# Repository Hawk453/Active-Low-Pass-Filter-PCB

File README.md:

# Second-Order Active Low-Pass Filter (LM741)  

## Overview  

This project implements a **second-order active low-pass filter** using the **LM741 operational amplifier**. The filter is designed in **KiCad** and is suitable for basic signal conditioning and noise filtering applications.  

The filter attenuates frequencies above a specified **cutoff frequency (fc)** while allowing lower-frequency signals to pass with minimal attenuation.  

## Schematic  

## PCB Layout  

Here’s a preview of the designed PCB:  

The filter circuit is built using a **Sallen-Key topology** and includes:  

- **Op-Amp**: LM741 (U1)  
- **Resistors**: R1, R2, R3, R4  
- **Capacitors**: C1, C2  
- **Input/Output**: J1, J2 (Coaxial connectors), J3 (Pin connector)  
- **Power Supply**: ±10V  

*(Replace component values and results below with your actual design)*

| Component | Value       |
|-----------|-------------|
| R1        | 3.3 kΩ      |
| R2        | 3.3 kΩ      |
| R3, R4    | 10 kΩ       |
| C1        | 10 nF       |
| C2        | 10 nF       |
| Cutoff    | ~4.8 kHz    |  

## Files Included  

📁 **KiCad Project Files**  
- Schematic: `Second_Order_Low_Pass_Filter_Ac.kicad_sch`  
- PDF Schematic: `Second_Order_Low_Pass_Filter_Ac.pdf`  
- PCB Layout: `Second_Order_Low_Pass_Filter_Ac.kicad_pcb`  

📁 **Fabrication Files**  
- **Gerber Files**: Ready for PCB manufacturing.  
- Drill files and fabrication layers included.  

📁 **Bill of Materials (BOM)**  
- Can be generated from KiCad (`Tools` -> `Generate BOM`).  

## How to Use  

1. **View Schematic and PCB**  
   - Open `.kicad_sch` and `.kicad_pcb` files in **KiCad** (v9.0.2 or newer).  

2. **Simulate (Optional)**  
   - Export netlist and simulate in a tool like LTspice or use KiCad’s simulator for basic analysis.  

3. **Fabricate PCB**  
   - Use the included **Gerber files** to manufacture the PCB through a PCB fabrication service.  

4. **Assemble the Circuit**  
   - Solder components as per the schematic and BOM.  
   - Power the board using ±10V.  

5. **Test the Filter**  
   - Apply test signals and verify the cutoff frequency response using an oscilloscope or signal analyzer.  

## Notes  

- The **LM741** is a general-purpose op-amp with limited bandwidth. For high-frequency applications, consider alternatives like TL072 or LM358.  
- This filter is ideal for **audio applications** or low-frequency signal conditioning tasks.  

## License  

GPL 3.0

## Acknowledgments  

Special thanks to the **KiCad community** for making open-source hardware design accessible!

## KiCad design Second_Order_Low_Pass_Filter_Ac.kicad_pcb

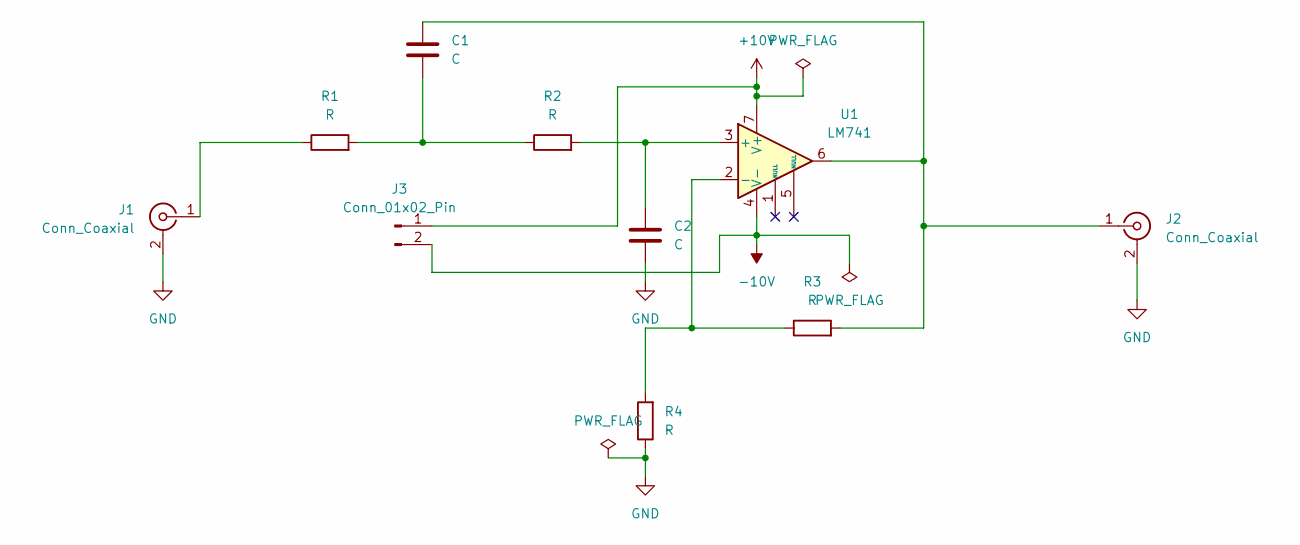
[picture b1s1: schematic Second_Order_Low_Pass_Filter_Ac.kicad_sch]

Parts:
C1, C2: C; C_Disc_D5.0mm_W2.5mm_P5.00mm
J1, J2: Conn_Coaxial; BNC_TEConnectivity_1478035_Horizontal
J3: Conn_01x02_Pin; Banana_Jack_2Pin
R1, R2, R3, R4: R; R_Axial_DIN0204_L3.6mm_D1.6mm_P7.62mm_Horizontal
U1: LM741; DIP-8_W7.62mm_LongPads

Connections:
+10V: J3.1, U1.7 (V+)
-10V: J3.2, U1.4 (V-)
GND: C2.2, J1.2 (Ext), J2.2 (Ext), R4.1
unnamed: C1.2, R1.2, R2.1
unnamed: J1.1 (In), R1.1
unnamed: C1.1, J2.1 (In), R3.2, U1.6
unnamed: C2.1, R2.2, U1.3 (+)
unnamed: R3.1, R4.2, U1.2 (-)

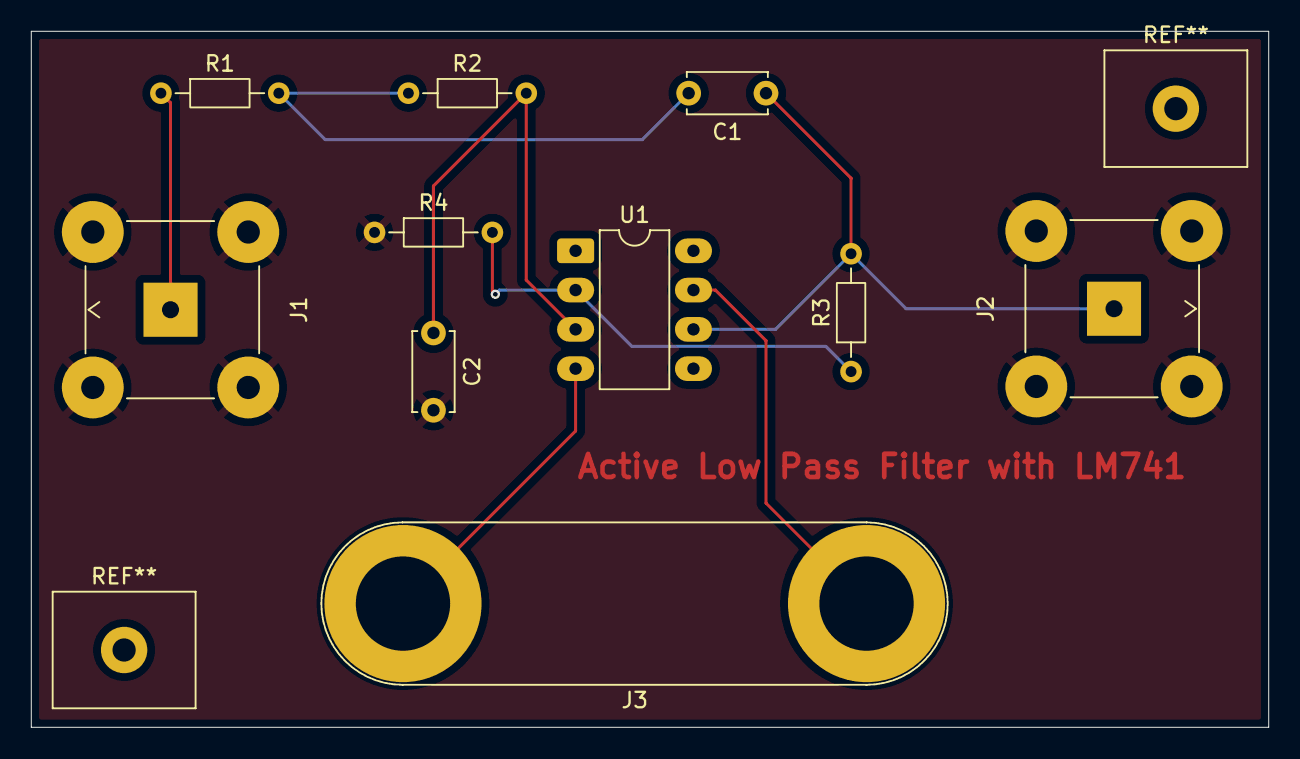
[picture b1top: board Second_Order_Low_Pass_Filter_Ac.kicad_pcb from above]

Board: 2 copper layers, 80.0 x 45.0 mm, 10 parts (0 on the bottom side), 8 nets.

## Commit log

2025-05-27 KiCAD files
